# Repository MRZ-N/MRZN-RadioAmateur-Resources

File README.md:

# MRZN-QSL-Receiver
### Receptor de la imagen QSL y la baliza de texto del satélite MRZN, con un Raspberry Pi Pico y un módulo RF4463PRO

Receptor de código y hardware abiertos para radioaficionados. Recibe dos emisiones del satélite MRZN:

* **La imagen QSL**, transmitida en paquetes SSDV, que se reconstruye en un archivo JPEG.
* **La baliza de texto**, una trama AX.25 con el indicativo del satélite.

El receptor **solo recibe**: el firmware no tiene ninguna función de transmisión.

Contenido del repositorio:

* `hardware/`: las placas, en KiCad, con los archivos de fabricación.
* `firmware/`: el firmware del Pico, el código fuente y los `.uf2` listos para cargar.
* `host/`: los programas del PC, en Python: consola, decodificador, carga del firmware y autoprueba.

---

## 1. Qué transmite el satélite

| Emisión | Formato | Cuándo |
|---|---|---|
| Baliza de texto | Trama AX.25 UI con el texto `HR0UNA` (indicativo actual del satélite) | Cada 5 s durante los pases en que el satélite emite su baliza |
| Imagen QSL | Paquetes SSDV de 72 o 128 bytes; la imagen se repite en bucle durante el pase | Durante los pases QSL que programa el equipo del MRZN |

Durante un pase QSL el satélite emite solo la imagen. La baliza de texto sale en otros pases.

### Parámetros del enlace descendente

| | |
|---|---|
| Frecuencia | 435.500 MHz (fija en el firmware) |
| Modulación | 2GFSK, 9600 baudios, desviación ±2400 Hz |
| Paquete | preámbulo de bits alternados · sincronía `0x7E` · longitud N (1 byte) · N bytes de datos · 2 bytes de cola |

Los N bytes de datos son, según la emisión, un paquete SSDV o la trama AX.25. Cada uno trae su propia comprobación: el CRC-32 de SSDV y el FCS de AX.25. El receptor solo acepta lo que la supera.

---

## 2. Hardware

### Placas

| Carpeta | Placa | Firmware |
|---|---|---|
| `hardware/placa_un_modulo/` | Un Pico con un módulo RF4463PRO | `rx_qsl_un_modulo.uf2` |
| `hardware/placa_dos_modulos/` | Un Pico con dos módulos; para recibir se usa el U2 | `rx_qsl_dos_modulos.uf2` |

Para solo recibir basta la placa de un módulo. Cada carpeta tiene el proyecto de KiCad (`RF4463PRO.kicad_pro`) y, en `production/`, los Gerber (`.zip`), la lista de materiales (`_bom.csv`) y las posiciones de montaje (`_positions.csv`).

### Componentes (placa de un módulo)

| Ref. | Componente |
|---|---|
| A1 | Raspberry Pi Pico |
| U1 | Módulo **RF4463PRO de 433 MHz** (la huella de la placa se llama `RF4463PRO-915`; es la misma huella, pero el módulo tiene que ser el de 433 MHz) |
| J1 | Conector SMA de borde, para la antena |
| R1, R2 | 10 kΩ (0805), de nSEL y SDN a 3V3 |
| C1 | 47 µF electrolítico |
| J2..J5 | Tiras de pines para acceso a señales del Pico |

### Conexiones

Placa de un módulo (bus SPI0 del Pico):

| RF4463PRO | SDO | SDI | SCLK | nSEL | nIRQ | SDN | VCC | GND |
|---|---|---|---|---|---|---|---|---|
| Pico | GP16 | GP19 | GP18 | GP17 | GP2 | GP3 | 3V3 (pin 36) | GND |

Placa de dos módulos: se recibe con el U2, en el bus SPI1. El U1 queda apagado.

| U2 | SDO | SDI | SCLK | nSEL | nIRQ | SDN |
|---|---|---|---|---|---|---|
| Pico | GP12 | GP11 | GP10 | GP13 | GP15 | GP14 |

También se puede montar sin placa, con cables, siguiendo la tabla de un módulo.

### Antena

Una antena de 70 cm (430–440 MHz) conectada al SMA. Una Yagi apuntada al satélite da el mejor resultado. Un preamplificador (LNA) de 435 MHz junto a la antena mejora la recepción, sobre todo con cables largos.

---

## 3. Instalación del software

Requisitos: **Python 3.9 o superior** y **pyserial**.

```bash
pip install -r host/requirements.txt
```

### El programa ssdv

La imagen QSL se reconstruye con [ssdv](https://codeberg.org/fsphil/ssdv), un programa libre para codificar y decodificar imágenes SSDV. Su código está en `herramientas/ssdv/`.

* **Windows:** `herramientas/ssdv.exe` ya viene compilado.
* **Linux / macOS:** compilarlo una vez:

  ```bash
  cd herramientas/ssdv
  make
  ```

Sin ssdv el receptor funciona igual y guarda la imagen en `.ssdv`, pero no la convierte a JPEG.

---

## 4. Cargar el firmware en el Pico

Con el Pico conectado por USB:

```bash
python host/flashear.py                        # placa de un módulo
python host/flashear.py --placa dos_modulos    # placa de dos módulos
```

El programa pone el Pico en modo de carga sin pulsar BOOTSEL, copia el `.uf2` y comprueba que arranca. Tiene que terminar en `LISTO`.

**Si el Pico es nuevo** (sin firmware con puerto serie), el modo de carga automático no funciona:

1. Desconectar el Pico.
2. Conectarlo con el botón **BOOTSEL** pulsado; aparece una unidad USB llamada `RPI-RP2`.
3. Ejecutar otra vez `python host/flashear.py`, o copiar a mano `firmware/uf2/rx_qsl_un_modulo.uf2` a esa unidad.

### Compilar el firmware

Con [PlatformIO](https://platformio.org/):

```bash
cd firmware/rx_qsl
pio run
```

Los `.uf2` quedan en `.pio/build/un_modulo/` y `.pio/build/dos_modulos/`.

---

## 5. Comprobar el receptor

```bash
python host/consola.py --comprobar
```

Salida de un receptor correcto:

```
Conectado a COM5: rx_qsl 1.0, placa un_modulo (U1)
Comprobando el receptor...
  [OK   ] Pico conectado por USB con el firmware rx_qsl  -- COM5
  [OK   ] Modulo RF4463PRO bien conectado (chip, SPI, SDN, nIRQ)  -- AUTOPRUEBA TODO BIEN: U1 BIEN (chip ok, SPI ok, SDN ok, nIRQ ok)
  [OK   ] Radio configurada para el enlace (2GFSK 9600, 435.500 MHz)  -- Si4463 listo
  [OK   ] Radio escuchando
  [INFO ] Nivel de senal en el canal ahora mismo  -- RSSI 15 (unidades del chip); 1 detecciones en 3 s
Resultado: TODO BIEN, listo para recibir.
```

| Comprobación | Qué revisa |
|---|---|
| Pico conectado | Que el puerto USB responde con el firmware `rx_qsl` |
| Módulo bien conectado | Cable a cable, con el propio chip: que contesta, que el SPI lee y escribe bien 6 patrones, que SDN lo apaga y lo enciende y que nIRQ cambia de nivel |
| Radio configurada | Que la configuración leída del chip es la del enlace (modulación, sincronía, paquete) |
| Radio escuchando | Que el chip está en recepción |
| Nivel de señal | Informativo: el RSSI del canal y las detecciones de los últimos 3 s |

---

## 6. Recibir

```bash
python host/consola.py
```

Dentro de la consola:

| Orden | Qué hace |
|---|---|
| `puertos` | Lista los puertos serie y marca el Pico |
| `conectar [PUERTO]` | Conecta con el Pico (sin puerto, lo busca solo) |
| `comprobar` | Las comprobaciones de la sección 5 |
| `escuchar [MINUTOS]` | Recibe la QSL y la baliza; Ctrl+C para parar antes |
| `estado` | Contadores del receptor |
| `reiniciar` | Reinicia la radio del módulo |
| `cristal VALOR` | Ajuste fino del cristal del módulo (0..127; avanzado) |
| `salir` | Cerrar |

También sin entrar en la consola: `python host/consola.py --escuchar 15` (15 minutos).

Ejemplo de un pase:

```
[13:46:45] BALIZA  MRZN>HR0UNA  "HR0UNA"  (RSSI 104)
[13:46:49] BALIZA  MRZN>HR0UNA  "HR0UNA"  (RSSI 106)
...
[13:48:07] QSL     MRZN imagen 2: 640x480, paquetes de 72 B
[13:48:07] QSL     MRZN imagen 2: 1 paquetes (todavia sin el ultimo)  (RSSI 105)
[13:48:12] QSL     MRZN imagen 2: 25 paquetes (todavia sin el ultimo)  (RSSI 102)
...
[13:48:55] QSL     MRZN imagen 2: 200 paquetes (todavia sin el ultimo)  (RSSI 100)
[13:48:59] QSL     MRZN imagen 2: 234/234 paquetes (COMPLETA)  (RSSI 100)
```

Si se pierden paquetes, la línea del último paquete indica cuántos faltan (por ejemplo `219/234 paquetes (faltan 15)`), y la cuenta sigue subiendo mientras la imagen se repite.

Lo recibido se guarda en `recepciones/<fecha_hora UTC>/`:

| Archivo | Contenido |
|---|---|
| `qsl/MRZN_imagen002.jpg` | La imagen QSL reconstruida |
| `qsl/MRZN_imagen002.ssdv` | Los paquetes SSDV recibidos, en orden |
| `balizas.txt` | Cada baliza recibida: hora UTC, origen>destino, texto y RSSI |
| `resumen.txt` | El resumen de la sesión |

Las imágenes se guardan cada 30 s durante la escucha y al terminar. Una imagen incompleta se reconstruye igual, con las zonas que faltan sin dibujar; como el satélite repite la imagen en bucle, los huecos se van llenando durante el pase.

---

## 7. Cómo se decodifica

```
antena ─► RF4463PRO (Si4463)                      ─► USB ─► PC (host/)
          · demodula 2GFSK 9600                            · ¿paquete SSDV con CRC-32 bueno?  ─► imagen QSL
          · detecta preámbulo y sincronía 0x7E             · ¿trama AX.25 UI con FCS bueno?   ─► baliza de texto
          · entrega los N bytes de datos                   · cualquier otra cosa              ─► se descarta
```

### En el Pico (`firmware/rx_qsl`)

* El Si4463 hace la demodulación, la detección del preámbulo y de la sincronía, y la extracción del paquete por longitud variable: el primer byte (N) dice cuántos datos vienen.
* El firmware vacía el FIFO del chip por trozos mientras llega el paquete, de modo que caben los 128 bytes aunque el FIFO sea de 64.
* Cada paquete pasa al PC por USB con su RSSI.
* Un vigilante comprueba cada 250 ms que el chip sigue de verdad en recepción y lo rearma si no.

### En el PC (`host/decodificador.py`)

**Imagen QSL (SSDV).** Cada paquete SSDV sin FEC tiene esta forma:

| Bytes | Campo |
|---|---|
| 0 | Sincronía `0x55` |
| 1 | Tipo: `0x67` sin FEC (`0x66` con FEC) |
| 2–5 | Indicativo, en base 40 |
| 6 | Número de imagen |
| 7–8 | Número de paquete |
| 9 / 10 | Ancho / alto de la imagen, en bloques de 16 píxeles |
| 11 | Banderas (bit 2: último paquete de la imagen) |
| ... | Datos JPEG |
| últimos 4 | CRC-32 sobre los bytes 1 a L−5 (L = longitud del paquete SSDV) |

`host/imagenes.py` junta los paquetes por indicativo y número de imagen, los ordena y llama a `ssdv -d` para obtener el JPEG.

**Baliza de texto (AX.25).** La trama AX.25 puede llegar como flujo HDLC (banderas, relleno de bits, NRZI y aleatorizador G3RUH 1 + x¹² + x¹⁷) o directamente en bytes; el decodificador prueba las dos formas. Se acepta solo si:

1. el FCS (CRC-16/X.25) es correcto;
2. es una trama UI (control `0x03`, PID `0xF0`);
3. el campo de información es una cabecera de 4 bytes seguida de un texto ASCII terminado en `0x00`.

Se muestran el origen, el destino y el texto.

---

## 8. Autoprueba sin radio

```bash
python host/autoprueba.py
```

Comprueba los decodificadores con la imagen de ejemplo `ejemplos/qsl_ejemplo.ssdv`:

* paquetes perdidos, repetidos, desordenados y uno corrupto;
* la reconstrucción en JPEG;
* una baliza AX.25 en sus dos formas;
* que se descarta lo que no es QSL ni baliza.

Tiene que terminar en `AUTOPRUEBA: TODO BIEN`.

---

## 9. Protocolo USB del firmware

Para quien quiera escribir su propio programa: mensajes SLIP sobre el puerto serie USB (115200 baudios). El primer byte indica el tipo.

| Sentido | Mensaje | Significado |
|---|---|---|
| PC → Pico | `P` | Estado |
| | `H` | Autoprueba de las conexiones |
| | `I` | Reiniciar la radio |
| | `X` + valor | Ajuste fino del cristal (0..127) |
| | `L` | Volver a escuchar |
| Pico → PC | `R` + RSSI (1 byte) + datos | Paquete recibido |
| | `V` + texto | Información o estado |
| | `W` + texto | Aviso |
| | `E` + texto | Error |
| | `K` | Orden terminada |

El estado (`P`) es una línea de campos `nombre=valor` separados por `|`: `paquetes`, `parciales`, `sinc_falsas`, `rearmes`, `vigilante`, `rssi_ahora`, `rssi`, `xo`, `arranques`. El RSSI está en unidades del chip.

---

## 10. Problemas frecuentes

| Síntoma | Qué hacer |
|---|---|
| `No se encuentra ningun Raspberry Pi Pico` | Revisar el cable USB (que sea de datos, no solo de carga) y cargar el firmware (sección 4) |
| `could not open port` | Otro programa tiene el puerto abierto: cerrarlo |
| La autoprueba marca `SPI` o `chip` con FALLO | Revisar SDI, SDO, SCLK y nSEL, y la alimentación de 3V3 del módulo |
| La autoprueba marca `SDN` o `nIRQ` con FALLO | Revisar ese cable concreto (GP3 / GP2 en la placa de un módulo) |
| `Radio configurada` con FALLO | Reiniciar la radio (orden `reiniciar` en la consola) o desconectar y conectar el Pico |
| Todo OK pero no llega nada | Comprobar la antena y su orientación, que el satélite esté sobre el horizonte y que sea un pase en que transmite; un LNA ayuda |
| Llegan balizas pero muy pocas | Señal débil: mejor antena, LNA, o esperar a un pase más alto |
| La imagen sale en `.ssdv` pero no en `.jpg` | Falta el programa ssdv (sección 3) |

---

## 11. Estructura del repositorio

```
MRZN-QSL-Receiver/
├── firmware/
│   ├── rx_qsl/                 proyecto PlatformIO
│   │   ├── src/main.cpp        recepción, USB, autoprueba, vigilante
│   │   ├── include/rf4463_rx.h driver de recepción del Si4463
│   │   └── include/radio_config.h  configuración de radio del Si4463 (WDS)
│   └── uf2/                    firmware compilado, listo para cargar
├── host/
│   ├── consola.py              la consola del receptor
│   ├── enlace.py               comunicación USB con el Pico
│   ├── decodificador.py        SSDV y AX.25
│   ├── imagenes.py             reconstrucción de la imagen QSL
│   ├── flashear.py             carga del firmware
│   ├── autoprueba.py           prueba de los decodificadores sin radio
│   └── requirements.txt
├── hardware/
│   ├── placa_un_modulo/        KiCad + fabricación
│   └── placa_dos_modulos/      KiCad + fabricación
├── herramientas/
│   ├── ssdv/                   código de ssdv (GPL-3.0)
│   └── ssdv.exe                ssdv compilado para Windows
├── ejemplos/
│   └── qsl_ejemplo.ssdv        imagen de prueba para la autoprueba
├── licencias/                  textos de las licencias de terceros
├── AVISOS_DE_TERCEROS.md       qué se usa de terceros y con qué licencia
└── LICENSE                     GPL-3.0
```

---

## 12. Licencia y créditos

* Este proyecto se distribuye bajo la licencia **GPL-3.0-only** (archivo `LICENSE`), sin la cláusula "o posterior", porque el firmware contiene código derivado de RadioHead, que es GPL-3.0.
* El driver del Si4463 (`rf4463_rx.h`) es obra derivada del driver RH_RF24 de la biblioteca **RadioHead** (<https://www.airspayce.com/mikem/arduino/RadioHead/>): el envío de órdenes con espera de CTS, el reinicio por SDN y la lectura del FIFO por trozos. Su cabecera conserva el aviso de copyright de RadioHead y detalla qué se modificó.
* La configuración del modem (`radio_config.h`) se calculó con **WDS** (Wireless Development Suite) de Silicon Labs; el repositorio solo contiene los valores resultantes. Para usar otra frecuencia hay que recalcularla con WDS.
* **ssdv**: <https://codeberg.org/fsphil/ssdv> (antes en GitHub), GPL-3.0 o posterior. Su código va sin modificar y conserva sus avisos de copyright originales.
* El símbolo y la huella del RF4463PRO vienen de SnapEDA (SnapMagic), bajo CC BY-SA 4.0 con su "Design Exception 1.0".
* El logotipo de MORAZAN-SAT de la serigrafía no está incluido en la licencia: no se puede usar fuera de estas placas sin permiso del proyecto, y quien fabrique una placa puede quitarlo.
* Los `.uf2` llevan además el núcleo Arduino para el RP2040 (ArduinoCore-mbed), Mbed OS, el SDK del Pico y las bibliotecas de GCC. Sus licencias, la fuente de cada uno y cómo se compiló `ssdv.exe` están en [`AVISOS_DE_TERCEROS.md`](AVISOS_DE_TERCEROS.md), y los textos completos en `licencias/`.

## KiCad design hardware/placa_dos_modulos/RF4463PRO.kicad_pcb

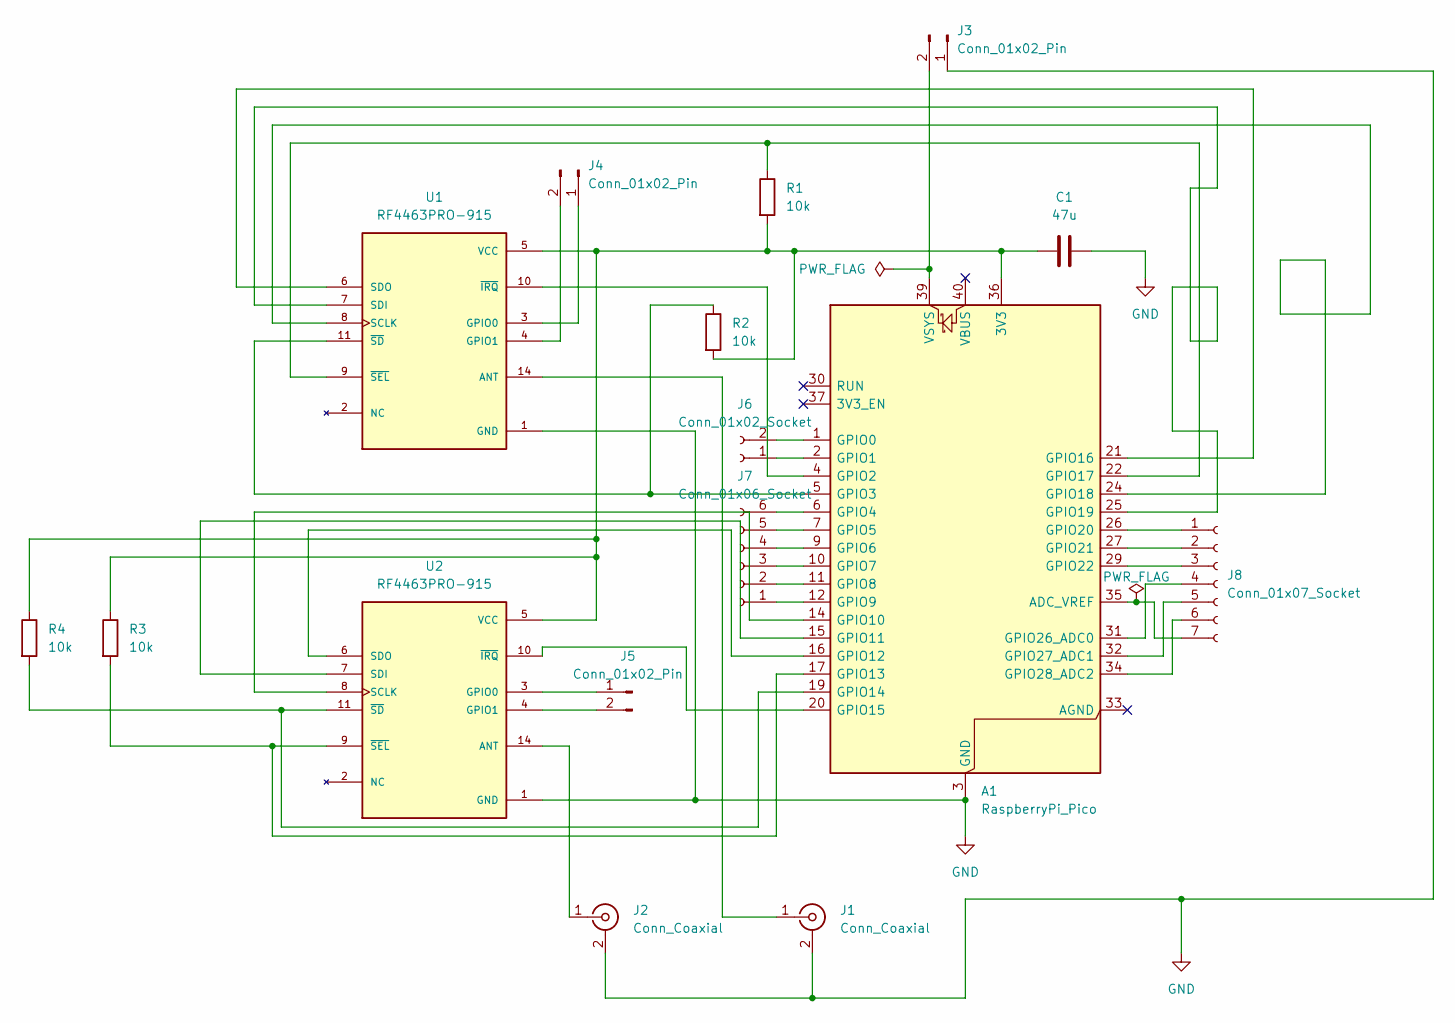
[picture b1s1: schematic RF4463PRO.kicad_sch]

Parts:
A1: RaspberryPi_Pico; RaspberryPi_Pico_SMD
C1: 47u; CP_Radial_D4.0mm_P2.00mm
J1, J2: Conn_Coaxial; SMA_Amphenol_132289_EdgeMount
J3: Conn_01x02_Pin; PinHeader_1x02_P2.54mm_Vertical
J4, J5: Conn_01x02_Pin; PinSocket_1x02_P2.54mm_Vertical
J6: Conn_01x02_Socket; PinSocket_1x02_P2.54mm_Vertical
J7: Conn_01x06_Socket; PinSocket_1x06_P2.54mm_Vertical
J8: Conn_01x07_Socket; PinSocket_1x07_P2.54mm_Vertical
R1, R2, R3, R4: 10k; R_0805_2012Metric_Pad1.20x1.40mm_HandSolder
U1, U2: RF4463PRO-915; XCVR_RF4463PRO-915; PARTREV V3.3

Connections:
GND: A1.3 (GND), A1.8 (GND), A1.13 (GND), A1.18 (GND), A1.23 (GND), A1.28 (GND), A1.38 (GND), C1.2, J1.2 (Ext), J2.2 (Ext), J3.1, U1.1 (GND), U1.12 (GND), U1.13 (GND), U2.1 (GND), U2.12 (GND), U2.13 (GND)
unnamed: A1.36 (3V3), C1.1, R1.2, R2.2, R3.1, R4.1, U1.5 (VCC), U2.5 (VCC)
unnamed: A1.35 (ADC_VREF), J8.7
unnamed: A1.1 (GPIO0), J6.2
unnamed: A1.2 (GPIO1), J6.1
unnamed: A1.4 (GPIO2), U1.10 (~IRQ)
unnamed: A1.5 (GPIO3), R2.1, U1.11 (~SD)
unnamed: A1.6 (GPIO4), J7.6
unnamed: A1.7 (GPIO5), J7.5
unnamed: A1.9 (GPIO6), J7.4
unnamed: A1.10 (GPIO7), J7.3
unnamed: A1.11 (GPIO8), J7.2
unnamed: A1.12 (GPIO9), J7.1
unnamed: A1.14 (GPIO10), U2.8 (SCLK)
unnamed: A1.15 (GPIO11), U2.7 (SDI)
unnamed: A1.16 (GPIO12), U2.6 (SDO)
unnamed: A1.17 (GPIO13), R3.2, U2.9 (~SEL)
unnamed: A1.19 (GPIO14), R4.2, U2.11 (~SD)
unnamed: A1.20 (GPIO15), U2.10 (~IRQ)
unnamed: A1.21 (GPIO16), U1.6 (SDO)
unnamed: A1.22 (GPIO17), R1.1, U1.9 (~SEL)
unnamed: A1.24 (GPIO18), U1.8 (SCLK)
unnamed: A1.25 (GPIO19), U1.7 (SDI)
unnamed: A1.26 (GPIO20), J8.1
unnamed: A1.27 (GPIO21), J8.2
unnamed: A1.29 (GPIO22), J8.3
unnamed: A1.31 (GPIO26_ADC0), J8.4
unnamed: A1.32 (GPIO27_ADC1), J8.5
unnamed: A1.34 (GPIO28_ADC2), J8.6
unnamed: A1.39 (VSYS), J3.2
unnamed: J1.1 (In), U1.14 (ANT)
unnamed: J2.1 (In), U2.14 (ANT)
unnamed: J4.1, U1.3 (GPIO0)
unnamed: J4.2, U1.4 (GPIO1)
unnamed: J5.1, U2.3 (GPIO0)
unnamed: J5.2, U2.4 (GPIO1)

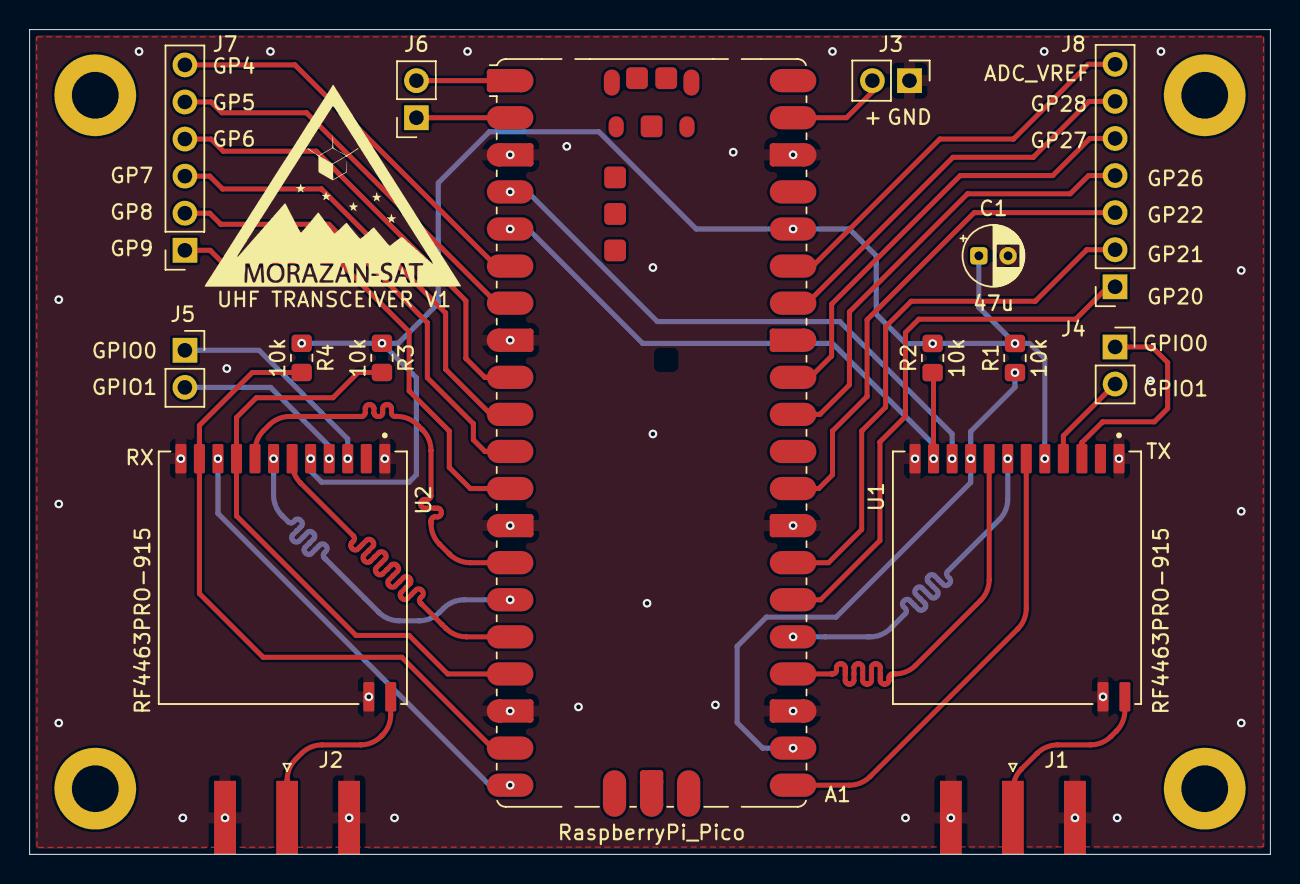
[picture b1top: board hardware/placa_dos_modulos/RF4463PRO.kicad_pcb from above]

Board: 4 copper layers, 85.0 x 56.5 mm, 16 parts (0 on the bottom side), 36 nets.

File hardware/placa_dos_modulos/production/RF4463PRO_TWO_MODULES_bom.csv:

Designator,Footprint,Quantity,Value,LCSC Part #
A1,RaspberryPi_Pico_SMD,1,RaspberryPi_Pico,
C1,CP_Radial_D4.0mm_P2.00mm,1,47u,
"J1, J2",SMA_Amphenol_132289_EdgeMount,2,Conn_Coaxial,
J3,PinHeader_1x02_P2.54mm_Vertical,1,Conn_01x02_Pin,
"J4, J5",PinSocket_1x02_P2.54mm_Vertical,2,Conn_01x02_Pin,
J6,PinSocket_1x02_P2.54mm_Vertical,1,Conn_01x02_Socket,
J7,PinSocket_1x06_P2.54mm_Vertical,1,Conn_01x06_Socket,
J8,PinSocket_1x07_P2.54mm_Vertical,1,Conn_01x07_Socket,
"R1, R2, R3, R4",0805,4,10k,
"U1, U2",XCVR_RF4463PRO-915,2,RF4463PRO-915,

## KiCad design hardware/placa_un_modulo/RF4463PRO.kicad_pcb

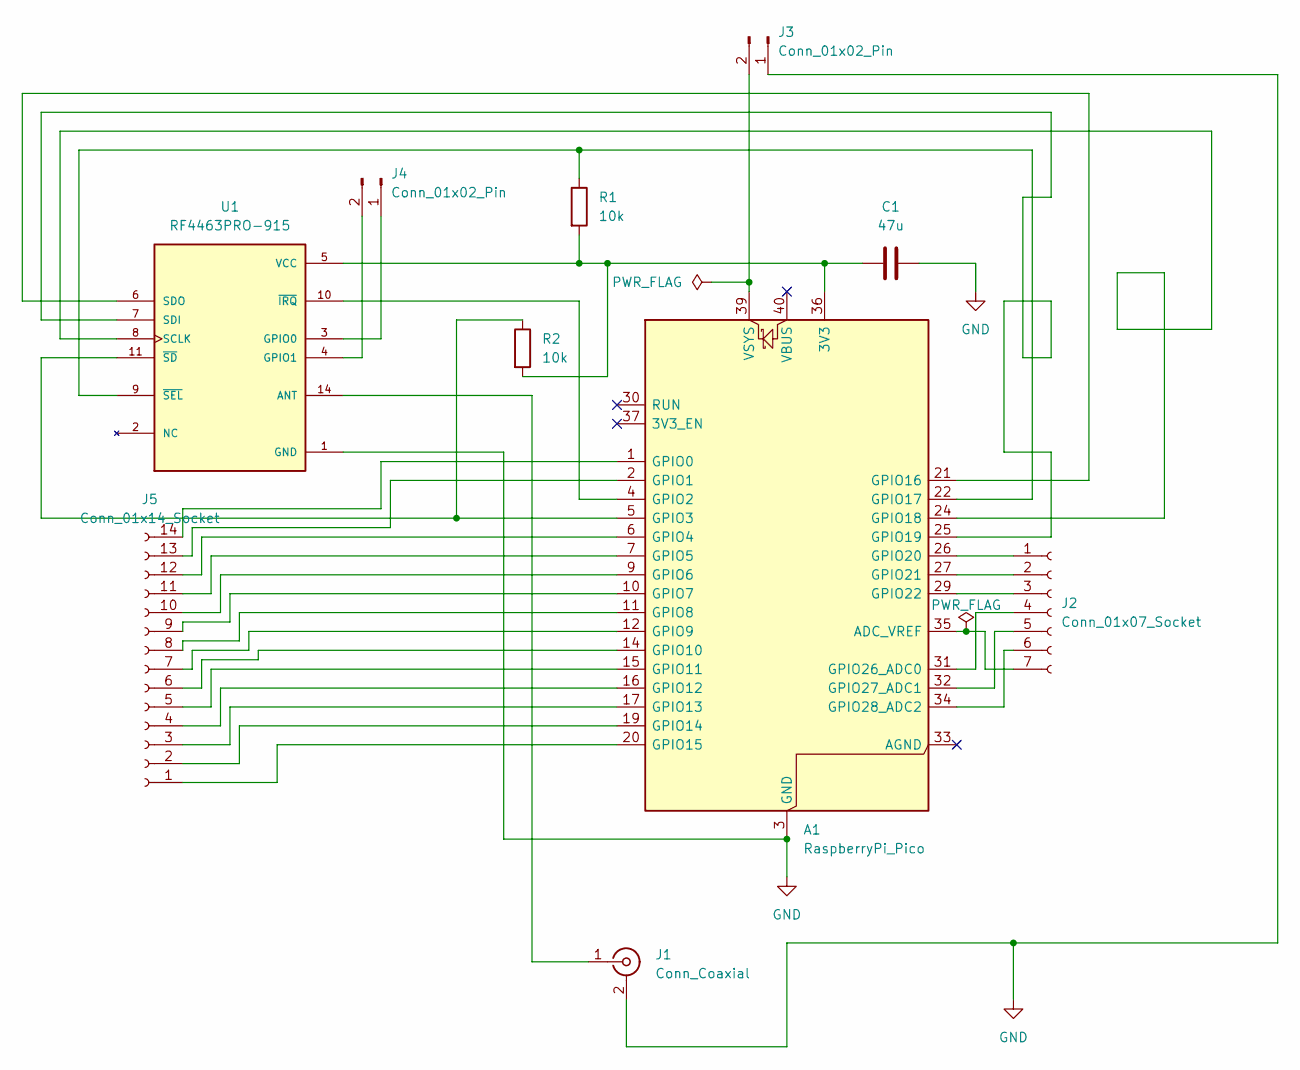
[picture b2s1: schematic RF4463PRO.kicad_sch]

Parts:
A1: RaspberryPi_Pico; RaspberryPi_Pico_SMD
C1: 47u; CP_Radial_D4.0mm_P2.00mm
J1: Conn_Coaxial; SMA_Amphenol_132289_EdgeMount
J2: Conn_01x07_Socket; PinSocket_1x07_P2.54mm_Vertical
J3: Conn_01x02_Pin; PinHeader_1x02_P2.54mm_Vertical
J4: Conn_01x02_Pin; PinSocket_1x02_P2.54mm_Vertical
J5: Conn_01x14_Socket; PinSocket_1x14_P2.54mm_Vertical
R1, R2: 10k; R_0805_2012Metric_Pad1.20x1.40mm_HandSolder
U1: RF4463PRO-915; XCVR_RF4463PRO-915; PARTREV V3.3

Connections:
GND: A1.3 (GND), A1.8 (GND), A1.13 (GND), A1.18 (GND), A1.23 (GND), A1.28 (GND), A1.38 (GND), C1.2, J1.2 (Ext), J3.1, U1.1 (GND), U1.12 (GND), U1.13 (GND)
unnamed: A1.36 (3V3), C1.1, R1.2, R2.2, U1.5 (VCC)
unnamed: A1.35 (ADC_VREF), J2.7
unnamed: A1.1 (GPIO0), J5.14
unnamed: A1.2 (GPIO1), J5.13
unnamed: A1.4 (GPIO2), U1.10 (~IRQ)
unnamed: A1.5 (GPIO3), R2.1, U1.11 (~SD)
unnamed: A1.6 (GPIO4), J5.12
unnamed: A1.7 (GPIO5), J5.11
unnamed: A1.9 (GPIO6), J5.10
unnamed: A1.10 (GPIO7), J5.9
unnamed: A1.11 (GPIO8), J5.8
unnamed: A1.12 (GPIO9), J5.7
unnamed: A1.14 (GPIO10), J5.6
unnamed: A1.15 (GPIO11), J5.5
unnamed: A1.16 (GPIO12), J5.4
unnamed: A1.17 (GPIO13), J5.3
unnamed: A1.19 (GPIO14), J5.2
unnamed: A1.20 (GPIO15), J5.1
unnamed: A1.21 (GPIO16), U1.6 (SDO)
unnamed: A1.22 (GPIO17), R1.1, U1.9 (~SEL)
unnamed: A1.24 (GPIO18), U1.8 (SCLK)
unnamed: A1.25 (GPIO19), U1.7 (SDI)
unnamed: A1.26 (GPIO20), J2.1
unnamed: A1.27 (GPIO21), J2.2
unnamed: A1.29 (GPIO22), J2.3
unnamed: A1.31 (GPIO26_ADC0), J2.4
unnamed: A1.32 (GPIO27_ADC1), J2.5
unnamed: A1.34 (GPIO28_ADC2), J2.6
unnamed: A1.39 (VSYS), J3.2
unnamed: J1.1 (In), U1.14 (ANT)
unnamed: J4.1, U1.3 (GPIO0)
unnamed: J4.2, U1.4 (GPIO1)

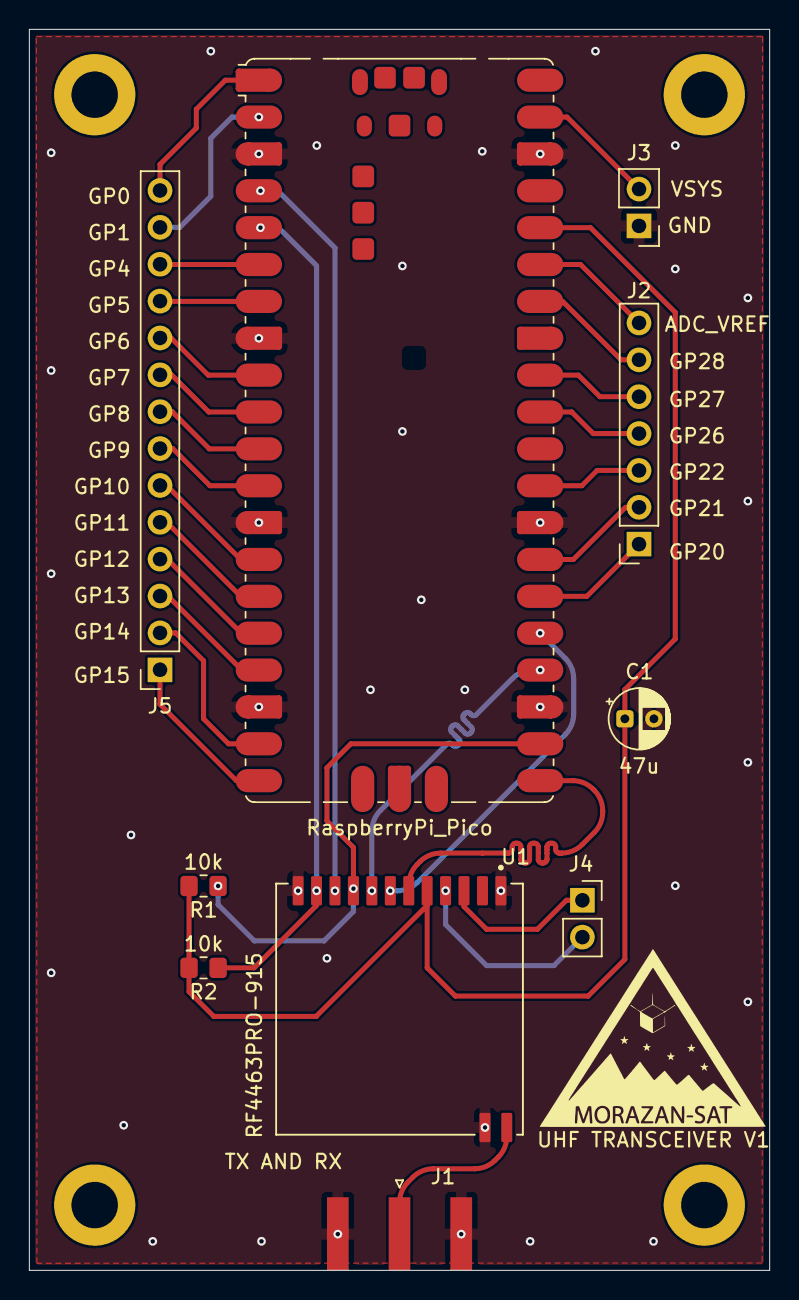
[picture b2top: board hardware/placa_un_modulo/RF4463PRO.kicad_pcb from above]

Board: 4 copper layers, 51.0 x 85.5 mm, 10 parts (0 on the bottom side), 33 nets.

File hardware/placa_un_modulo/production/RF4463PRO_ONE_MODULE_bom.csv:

Designator,Footprint,Quantity,Value,LCSC Part #
A1,RaspberryPi_Pico_SMD,1,RaspberryPi_Pico,
C1,CP_Radial_D4.0mm_P2.00mm,1,47u,
J1,SMA_Amphenol_132289_EdgeMount,1,Conn_Coaxial,
J2,PinSocket_1x07_P2.54mm_Vertical,1,Conn_01x07_Socket,
J3,PinHeader_1x02_P2.54mm_Vertical,1,Conn_01x02_Pin,
J4,PinSocket_1x02_P2.54mm_Vertical,1,Conn_01x02_Pin,
J5,PinSocket_1x14_P2.54mm_Vertical,1,Conn_01x14_Socket,
"R1, R2",0805,2,10k,
U1,XCVR_RF4463PRO-915,1,RF4463PRO-915,

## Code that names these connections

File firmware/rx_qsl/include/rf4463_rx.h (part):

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 * propia comprobacion (el CRC-32 de SSDV y el FCS de AX.25), y el programa del
 * PC solo acepta lo que la pasa.
 *
 * Antena: en el RF4463PRO los GPIO2/GPIO3 del chip mueven el conmutador de
 * antena del modulo (GPIO2 = recepcion, GPIO3 = transmision; hoja de datos del
 * modulo, pagina 5).  Se configuran con las funciones automaticas RX_STATE /
 * TX_STATE para que el propio chip lo maneje.
 */
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    void conmutador_antena()
    {
        uint8_t gpio[7] = {
            RF_GPIO_TRISTATE,       /* GPIO0 -- sin conectar */
            RF_GPIO_TRISTATE,       /* GPIO1 -- sin conectar */
            RF_GPIO_RX_STATE,       /* GPIO2 -- conmutador: recepcion */
            RF_GPIO_TX_STATE,       /* GPIO3 -- conmutador: transmision (nunca se usa) */
            RF_GPIO_NO_CHANGE,      /* nIRQ */
            RF_GPIO_NO_CHANGE,      /* SDO */
            0x00
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

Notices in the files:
firmware/rx_qsl/include/rf4463_rx.h:
SPDX-License-Identifier: GPL-3.0-only
Obra derivada del driver RH_RF24 de la biblioteca RadioHead (version 1.145):
RadioHead Copyright (C) 2011-2022 Mike McCauley
RH_RF24.cpp  Copyright (C) 2011 Mike McCauley
RH_RF24.h Copyright (C) 2014 Mike McCauley
RadioHead se distribuye bajo la GNU GPL version 3 (o con licencia
comercial); este archivo se distribuye bajo la GNU GPL version 3.
los terminos de la GNU General Public License version 3, publicada por la
General Public License (archivo LICENSE) para mas detalles.
